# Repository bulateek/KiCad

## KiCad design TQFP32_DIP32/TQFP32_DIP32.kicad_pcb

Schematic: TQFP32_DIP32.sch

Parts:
J1.1: DIP_LEFT; PinHeader_1x14_P2.54mm_Vertical
J1.2: DIP_RIGHT; PinHeader_1x14_P2.54mm_Vertical
U1: ATmega328P-AU; TQFP-32_7x7mm_P0.8mm

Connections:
/AREF: J1.2.7, U1.20 (AREF)
/AVCC: J1.2.6, U1.18 (AVCC)
/GND: J1.1.8, J1.2.8, U1.3 (GND), U1.5 (GND), U1.21 (GND)
/PB0: J1.1.14, U1.12 (PB0)
/PB1: J1.2.1, U1.13 (PB1)
/PB2: J1.2.2, U1.14 (PB2)
/PB3: J1.2.3, U1.15 (PB3)
/PB4: J1.2.4, U1.16 (PB4)
/PB5: J1.2.5, U1.17 (PB5)
/PB6: J1.1.9, U1.7 (XTAL1/PB6)
/PB7: J1.1.10, U1.8 (XTAL2/PB7)
/PC0: J1.2.9, U1.23 (PC0)
/PC1: J1.2.10, U1.24 (PC1)
/PC2: J1.2.11, U1.25 (PC2)
/PC3: J1.2.12, U1.26 (PC3)
/PC4: J1.2.13, U1.27 (PC4)
/PC5: J1.2.14, U1.28 (PC5)
/PC6: J1.1.1, U1.29 (~RESET~/PC6)
/PD0: J1.1.2, U1.30 (PD0)
/PD1: J1.1.3, U1.31 (PD1)
/PD2: J1.1.4, U1.32 (PD2)
/PD3: J1.1.5, U1.1 (PD3)
/PD4: J1.1.6, U1.2 (PD4)
/PD5: J1.1.11, U1.9 (PD5)
/PD6: J1.1.12, U1.10 (PD6)
/PD7: J1.1.13, U1.11 (PD7)
/VCC: J1.1.7, U1.4 (VCC), U1.6 (VCC)

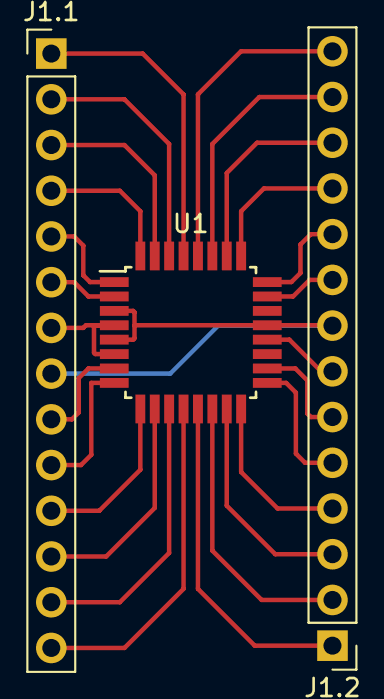
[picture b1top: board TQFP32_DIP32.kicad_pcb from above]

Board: 2 copper layers, 3 parts (0 on the bottom side), 27 nets.

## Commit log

2018-11-16 TQFP32_DIP32 first version
